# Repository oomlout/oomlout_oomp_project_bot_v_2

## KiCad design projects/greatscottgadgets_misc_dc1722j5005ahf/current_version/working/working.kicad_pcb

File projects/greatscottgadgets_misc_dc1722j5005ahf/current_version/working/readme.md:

# misc
 
## summary 
* id: greatscottgadgets_misc_dc1722j5005ahf
* user: greatscottgadgets
* name: misc
* board: dc1722j5005ahf
* repo: https://github.com/greatscottgadgets/misc
* src_file_repo_kicad_pcb: evaluation-boards/DC1722J5005AHF/DC1722J5005AHF.kicad_pcb
* src_file_repo_kicad_pcb_link: https://github.com/greatscottgadgets/misc/tree/master/evaluation-boards/DC1722J5005AHF/DC1722J5005AHF.kicad_pcb

* src_file_repo_sch: evaluation-boards/DC1722J5005AHF/DC1722J5005AHF.sch
* src_file_repo_sch_link: https://github.com/greatscottgadgets/misc/tree/master/evaluation-boards/DC1722J5005AHF/DC1722J5005AHF.sch
* full details link: https://github.com/oomlout/oomlout_oomp_project_bot_v_2/tree/main/projects/greatscottgadgets_misc_dc1722j5005ahf/current_version/working

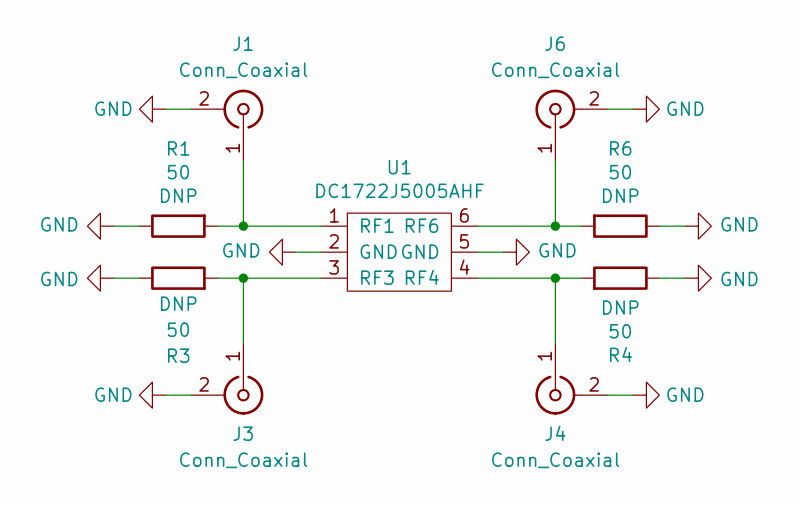
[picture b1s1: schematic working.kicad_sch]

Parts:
J1, J3, J4, J6: Conn_Coaxial; SMA-73251-2120
R1, R3, R4, R6: 50; R_0402_1005Metric
U1: DC1722J5005AHF; Anaren_0805_2012Metric-6

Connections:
GND: J1.2 (Ext), J3.2 (Ext), J4.2 (Ext), J6.2 (Ext), R1.1, R3.1, R4.1, R6.1, U1.2 (GND), U1.5 (GND)
unnamed: J1.1 (In), R1.2, U1.1 (RF1)
unnamed: J3.1 (In), R3.2, U1.3 (RF3)
unnamed: J4.1 (In), R4.2, U1.4 (RF4)
unnamed: J6.1 (In), R6.2, U1.6 (RF6)

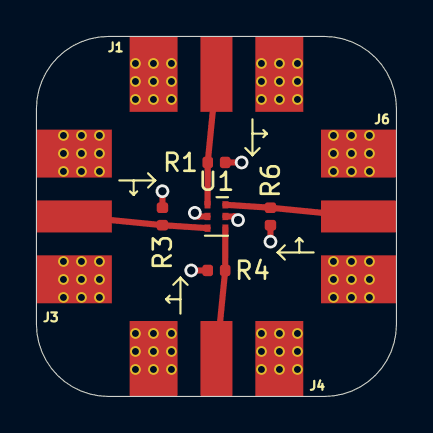
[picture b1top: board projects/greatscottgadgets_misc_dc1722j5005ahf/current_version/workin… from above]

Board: 4 copper layers, 20.0 x 20.0 mm, 9 parts (0 on the bottom side), 5 nets.

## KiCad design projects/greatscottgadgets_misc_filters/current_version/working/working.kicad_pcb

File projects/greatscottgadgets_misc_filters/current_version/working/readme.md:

# misc
 
## summary 
* id: greatscottgadgets_misc_filters
* user: greatscottgadgets
* name: misc
* board: filters
* repo: https://github.com/greatscottgadgets/misc
* src_file_repo_kicad_pcb: evaluation-boards/filters/filters.kicad_pcb
* src_file_repo_kicad_pcb_link: https://github.com/greatscottgadgets/misc/tree/master/evaluation-boards/filters/filters.kicad_pcb

* src_file_repo_sch: evaluation-boards/filters/filters.sch
* src_file_repo_sch_link: https://github.com/greatscottgadgets/misc/tree/master/evaluation-boards/filters/filters.sch
* full details link: https://github.com/oomlout/oomlout_oomp_project_bot_v_2/tree/main/projects/greatscottgadgets_misc_filters/current_version/working

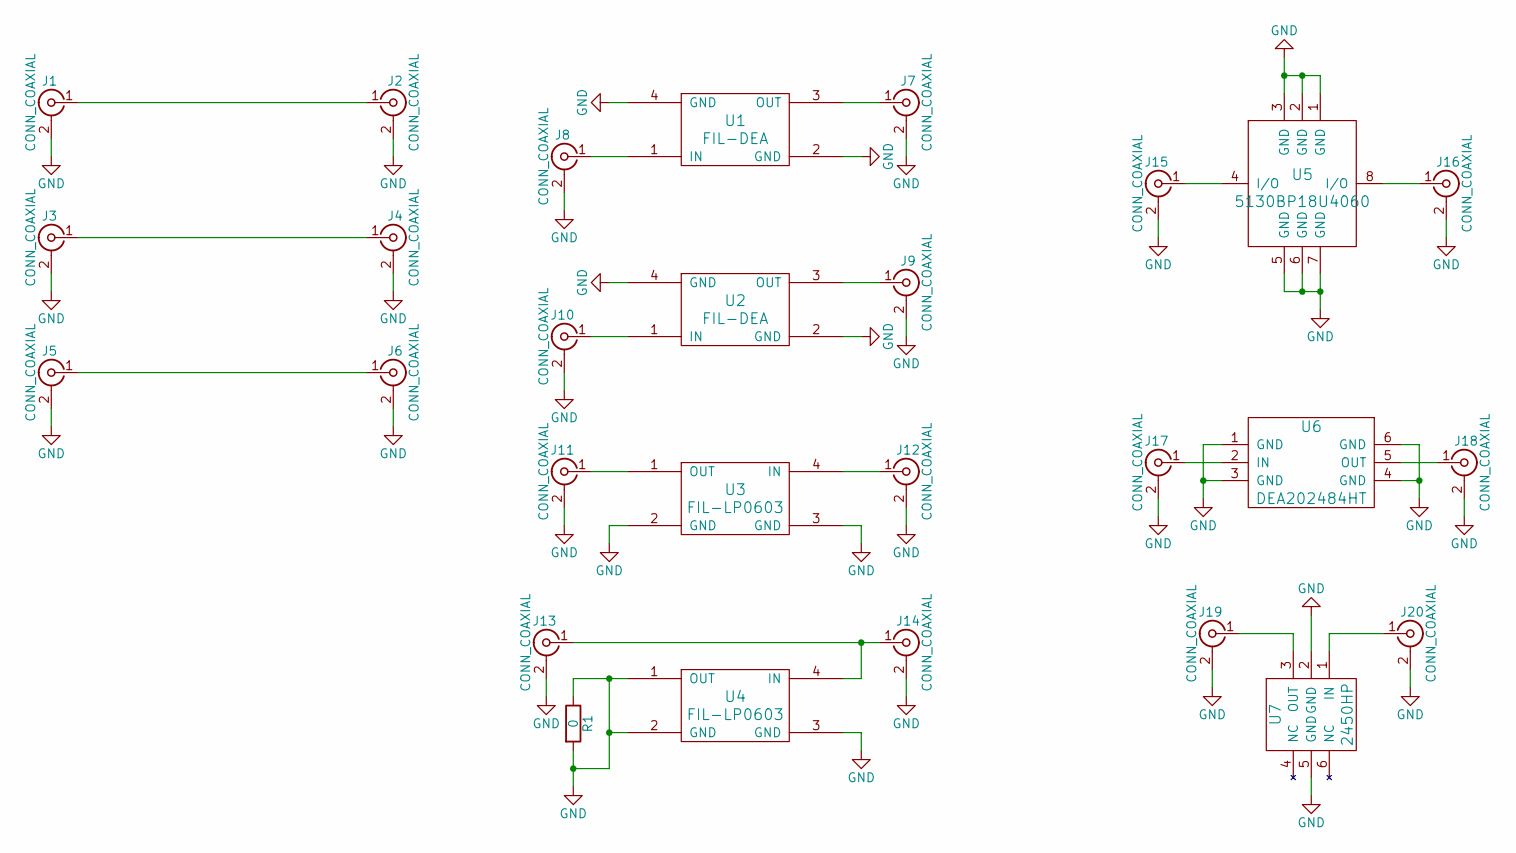
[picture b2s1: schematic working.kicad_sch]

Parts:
J1, J2, J3, J4, J5, J6, J7, J8, J9, J10, J11, J12, J13, J14, J15, J16, J17, J18, J19, J20: CONN_COAXIAL; SMA-EDGE
R1: 0; 0402
U1, U2: FIL-DEA; FIL-DEA-0603
U3, U4: FIL-LP0603; LP0603
U5: 5130BP18U4060
U6: DEA202484HT
U7: 2450HP; 2500BL14M100

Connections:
GND: J1.2 (Ext), J2.2 (Ext), J3.2 (Ext), J4.2 (Ext), J5.2 (Ext), J6.2 (Ext), J7.2 (Ext), J8.2 (Ext), J9.2 (Ext), J10.2 (Ext), J11.2 (Ext), J12.2 (Ext), J13.2 (Ext), J14.2 (Ext), J15.2 (Ext), J16.2 (Ext), J17.2 (Ext), J18.2 (Ext), J19.2 (Ext), J20.2 (Ext), R1.1, R1.2, U1.2 (GND), U1.4 (GND), U2.2 (GND), U2.4 (GND), U3.2 (GND), U3.3 (GND), U4.1 (OUT), U4.2 (GND), U4.3 (GND), U5.1 (GND), U5.2 (GND), U5.3 (GND), U5.5 (GND), U5.6 (GND), U5.7 (GND), U6.1 (GND), U6.3 (GND), U6.4 (GND), U6.6 (GND), U7.2 (GND), U7.5 (GND)
unnamed: J1.1 (In), J2.1 (In)
unnamed: J3.1 (In), J4.1 (In)
unnamed: J5.1 (In), J6.1 (In)
unnamed: J7.1 (In), U1.3 (OUT)
unnamed: J8.1 (In), U1.1 (IN)
unnamed: J9.1 (In), U2.3 (OUT)
unnamed: J10.1 (In), U2.1 (IN)
unnamed: J11.1 (In), U3.1 (OUT)
unnamed: J12.1 (In), U3.4 (IN)
unnamed: J13.1 (In), J14.1 (In), U4.4 (IN)
unnamed: J15.1 (In), U5.4 (I/O)
unnamed: J16.1 (In), U5.8 (I/O)
unnamed: J17.1 (In), U6.2 (IN)
unnamed: J18.1 (In), U6.5 (OUT)
unnamed: J19.1 (In), U7.3 (OUT)
unnamed: J20.1 (In), U7.1 (IN)

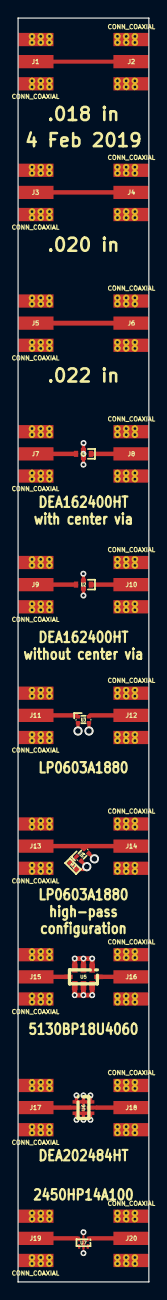
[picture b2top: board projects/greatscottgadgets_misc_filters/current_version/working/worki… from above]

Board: 4 copper layers, 15.0 x 145.0 mm, 28 parts (0 on the bottom side), 17 nets.

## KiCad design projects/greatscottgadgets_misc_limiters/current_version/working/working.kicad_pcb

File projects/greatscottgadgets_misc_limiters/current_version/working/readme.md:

# misc
 
## summary 
* id: greatscottgadgets_misc_limiters
* user: greatscottgadgets
* name: misc
* board: limiters
* repo: https://github.com/greatscottgadgets/misc
* src_file_repo_kicad_pcb: evaluation-boards/limiters/limiters.kicad_pcb
* src_file_repo_kicad_pcb_link: https://github.com/greatscottgadgets/misc/tree/master/evaluation-boards/limiters/limiters.kicad_pcb
* src_file_repo_kicad_sch: evaluation-boards/limiters/limiters.kicad_sch
* src_file_repo_kicad_sch_link: https://github.com/greatscottgadgets/misc/tree/master/evaluation-boards/limiters/limiters.kicad_sch

* src_file_repo_sch: evaluation-boards/limiters/limiters.sch
* src_file_repo_sch_link: https://github.com/greatscottgadgets/misc/tree/master/evaluation-boards/limiters/limiters.sch
* full details link: https://github.com/oomlout/oomlout_oomp_project_bot_v_2/tree/main/projects/greatscottgadgets_misc_limiters/current_version/working

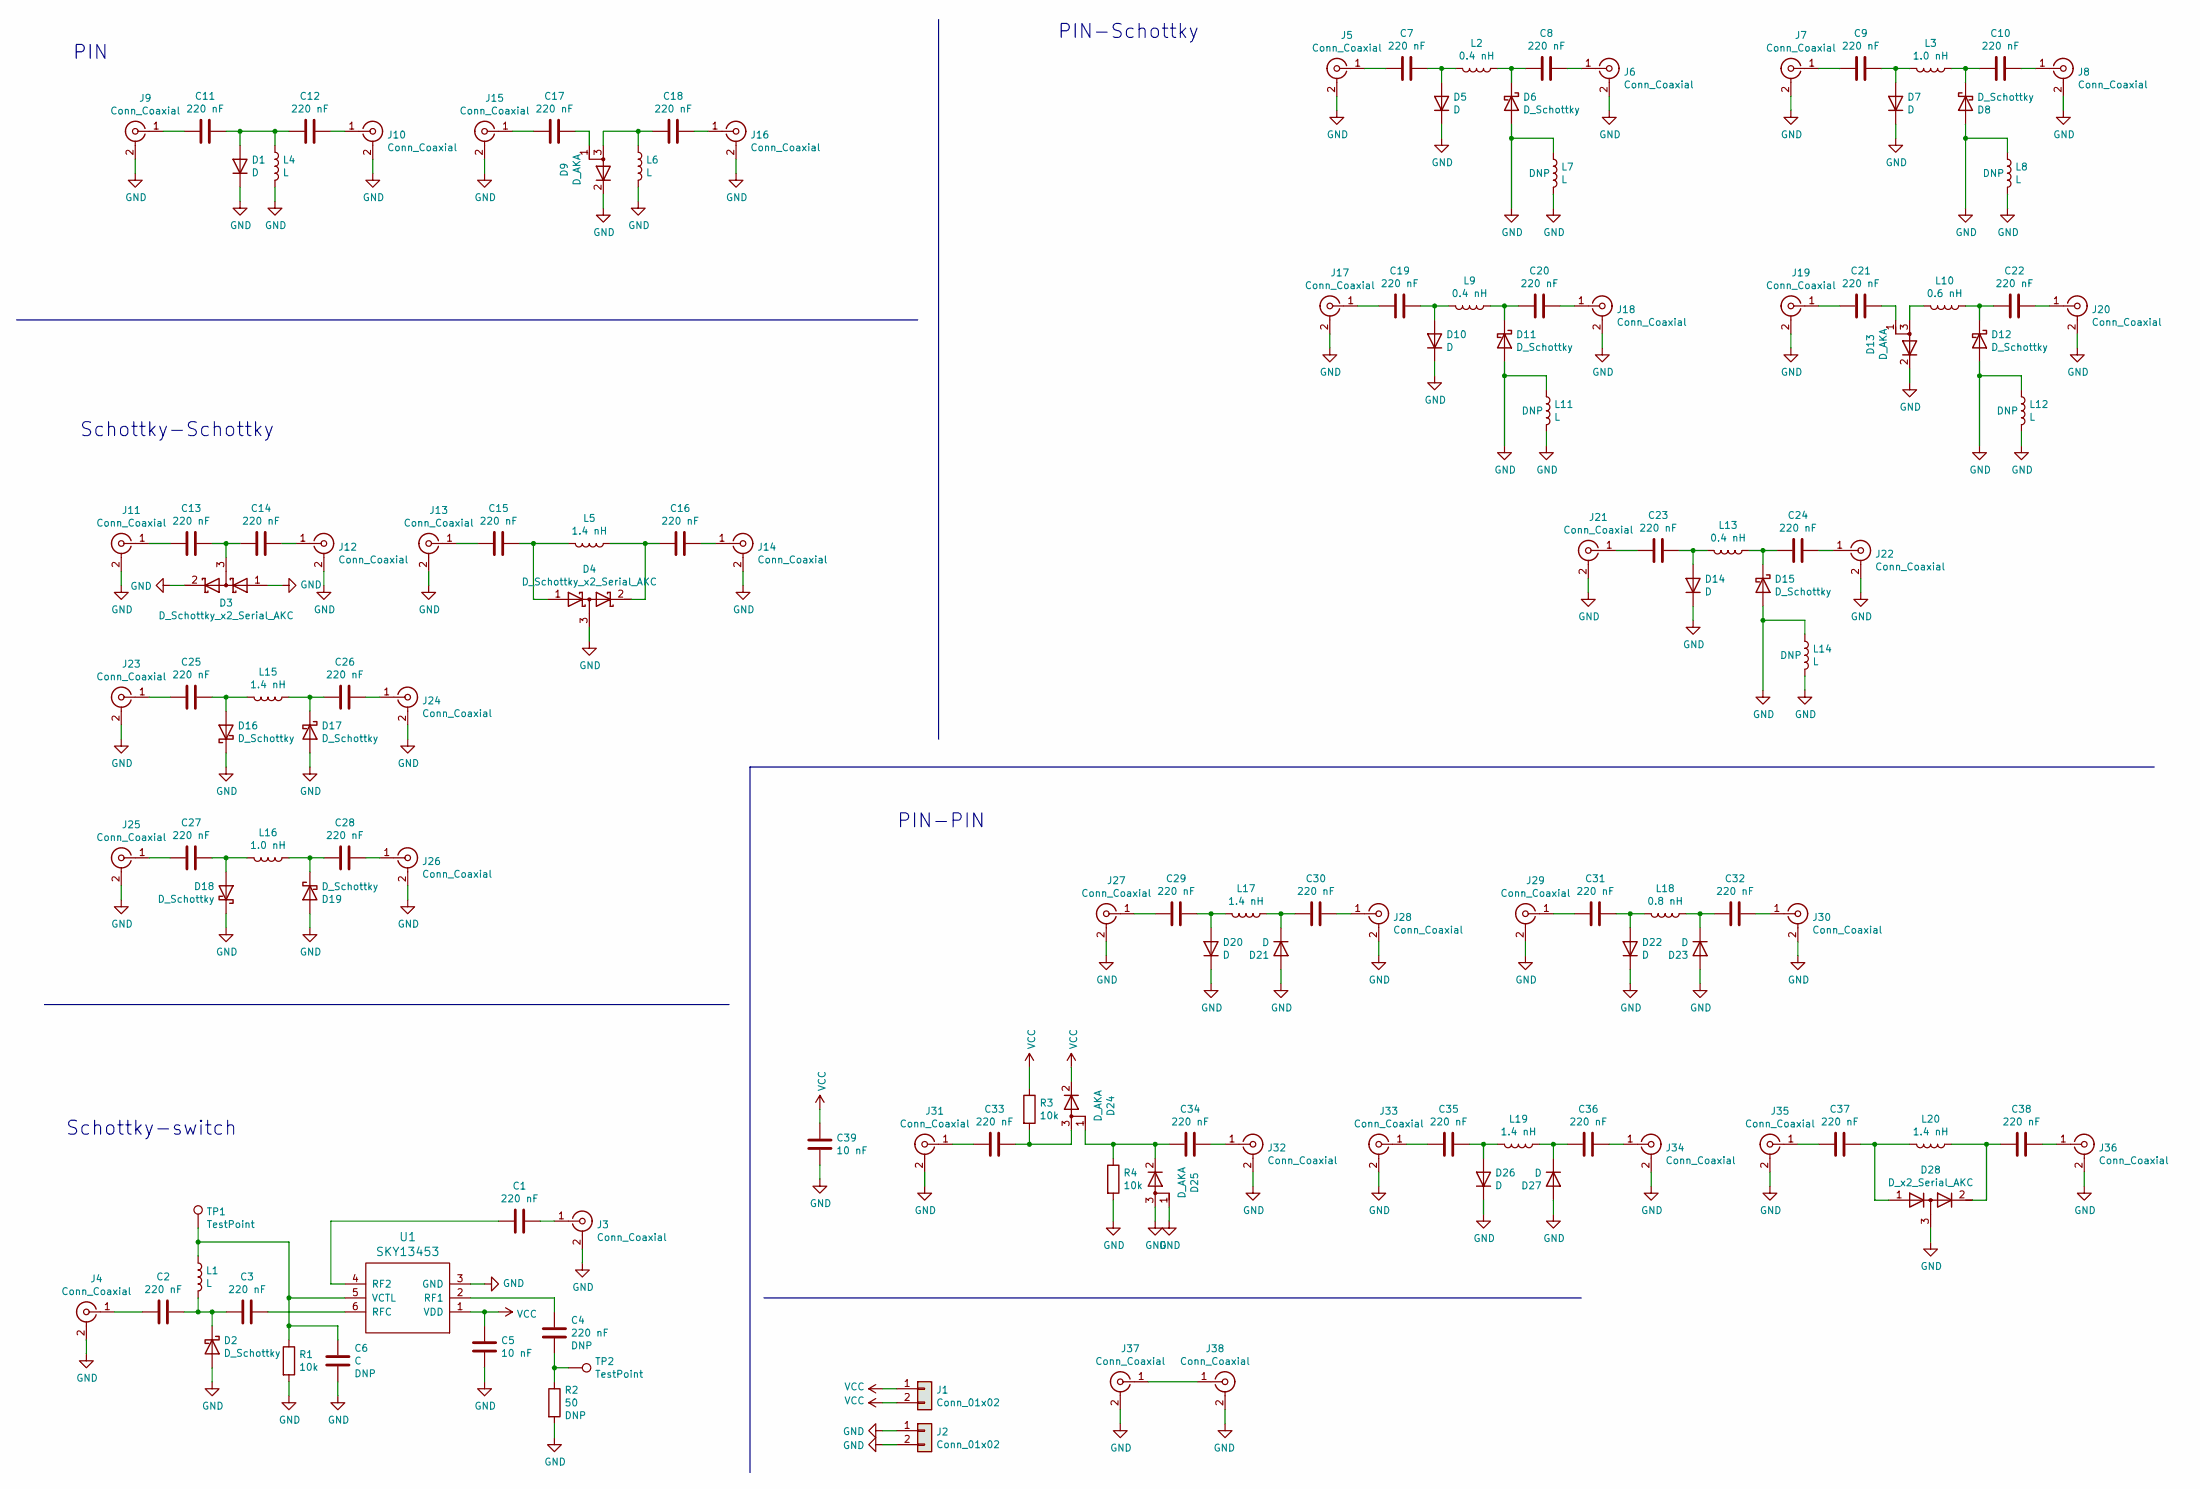
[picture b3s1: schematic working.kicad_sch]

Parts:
C1, C2, C3, C4, C7, C8, C9, C10, C11, C12, C13, C14, C15, C16, C17, C18, C19, C20, C21, C22, C23, C24, C25, C26, C27, C28, C29, C30, C31, C32, C33, C34, C35, C36, C37, C38: 220 nF; C_0201_0603Metric_Pad0.64x0.40mm_HandSolder; Part Number GRM033R61A224KE90D
C5, C39: 10 nF; C_0402_1005Metric_Pad0.74x0.62mm_HandSolder
C6: C; C_0402_1005Metric_Pad0.74x0.62mm_HandSolder
D1, D14, D22, D23: D; SMP1345-087LF; Part Number SMP1345-087LF
D2, D6, D11, D12, D15, D16, D17: D_Schottky; D_SOD-923; Part Number JDH2S02FSTPL3
D3, D4: D_Schottky_x2_Serial_AKC; SOT-23; Part Number BAT1504RE6152HTSA1
D5, D20, D21: D; D_0201_0603Metric_Pad0.64x0.40mm_HandSolder; Part Number NSDP301MX3T5G
D7: D; D_0201_0603Metric_Pad0.64x0.40mm_HandSolder; Part Number BAR9002ELSE6327XTSA1
D8, D18, D19: D_Schottky; D_0201_0603Metric_Pad0.64x0.40mm_HandSolder; Part Number BAT2402LSE6327XTSA1
D9, D13, D24, D25: D_AKA; SMP1304-085LF; Part Number SMP1304-085LF
D10, D26, D27: D; D_0402_1005Metric_Pad0.77x0.64mm_HandSolder; Part Number SMP1302-040LF
D28: D_x2_Serial_AKC; SOT-23; Part Number SMP1304-005LF
J1, J2: Conn_01x02; PinHeader_1x02_P2.54mm_Vertical
J3, J4, J5, J6, J7, J8, J9, J10, J11, J12, J13, J14, J15, J16, J17, J18, J19, J20, J21, J22, J23, J24, J25, J26, J27, J28, J29, J30, J31, J32, J33, J34, J35, J36, J37, J38: Conn_Coaxial; SMA-EDGE; Part Number CONSMA003.062
L1, L4, L6, L7, L8, L11, L12, L14: L; L_0603_1608Metric_Pad1.05x0.95mm_HandSolder; Part Number BRL1608T100M
L2, L9, L13: 0.4 nH; L_0201_0603Metric_Pad0.64x0.40mm_HandSolder; Part Number LQP03HQ0N4W02D
L3, L16: 1.0 nH; L_0201_0603Metric_Pad0.64x0.40mm_HandSolder; Part Number LQP03HQ1N0W02D
L5, L15, L17, L19, L20: 1.4 nH; L_0201_0603Metric_Pad0.64x0.40mm_HandSolder; Part Number LQP03HQ1N4W02D
L10: 0.6 nH; L_0201_0603Metric_Pad0.64x0.40mm_HandSolder; Part Number LQP03HQ0N6W02D
L18: 0.8 nH; L_0201_0603Metric_Pad0.64x0.40mm_HandSolder; Part Number LQP03HQ0N8W02D
R1, R3, R4: 10k; R_0402_1005Metric_Pad0.72x0.64mm_HandSolder
R2: 50; R_0402_1005Metric_Pad0.72x0.64mm_HandSolder
TP1, TP2: TestPoint; TESTPOINT-50MIL
U1: SKY13453; SKY13350-385LF; Part Number SKY13453-385LF

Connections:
GND: C5.1, C6.2, C39.1, D1.1 (K), D2.2 (A), D3.1 (A), D3.2 (K), D4.3 (common), D5.1 (K), D6.2 (A), D7.1 (K), D8.2 (A), D9.2 (K), D10.1 (K), D11.2 (A), D12.2 (A), D13.2 (K), D14.1 (K), D15.2 (A), D16.1 (K), D17.2 (A), D18.1 (K), D19.2 (A), D20.1 (K), D21.2 (A), D22.1 (K), D23.2 (A), D25.1 (A), D25.3 (A), D26.1 (K), D27.2 (A), D28.3 (common), J2.1, J2.2, J3.2 (Ext), J4.2 (Ext), J5.2 (Ext), J6.2 (Ext), J7.2 (Ext), J8.2 (Ext), J9.2 (Ext), J10.2 (Ext), J11.2 (Ext), J12.2 (Ext), J13.2 (Ext), J14.2 (Ext), J15.2 (Ext), J16.2 (Ext), J17.2 (Ext), J18.2 (Ext), J19.2 (Ext), J20.2 (Ext), J21.2 (Ext), J22.2 (Ext), J23.2 (Ext), J24.2 (Ext), J25.2 (Ext), J26.2 (Ext), J27.2 (Ext), J28.2 (Ext), J29.2 (Ext), J30.2 (Ext), J31.2 (Ext), J32.2 (Ext), J33.2 (Ext), J34.2 (Ext), J35.2 (Ext), J36.2 (Ext), J37.2 (Ext), J38.2 (Ext), L4.2, L6.2, L7.1, L7.2, L8.1, L8.2, L11.1, L11.2, L12.1, L12.2, L14.1, L14.2, R1.2, R2.2, R4.2, U1.3 (GND)
unnamed: C1.1, J3.1 (In)
unnamed: C1.2, U1.4 (RF2)
unnamed: C2.1, C3.2, D2.1 (K), L1.2
unnamed: C2.2, J4.1 (In)
unnamed: C3.1, U1.6 (RFC)
unnamed: C4.1, R2.1, TP2.1
unnamed: C4.2, U1.2 (RF1)
unnamed: C6.1, L1.1, R1.1, TP1.1, U1.5 (VCTL)
unnamed: C7.1, D5.2 (A), L2.2
unnamed: C7.2, J5.1 (In)
unnamed: C8.1, J6.1 (In)
unnamed: C8.2, D6.1 (K), L2.1
unnamed: C9.1, D7.2 (A), L3.2
unnamed: C9.2, J7.1 (In)
unnamed: C10.1, J8.1 (In)
unnamed: C10.2, D8.1 (K), L3.1
unnamed: C11.1, C12.2, D1.2 (A), L4.1
unnamed: C11.2, J9.1 (In)
unnamed: C12.1, J10.1 (In)
unnamed: C13.1, C14.2, D3.3 (common)
unnamed: C13.2, J11.1 (In)
unnamed: C14.1, J12.1 (In)
unnamed: C15.1, D4.1 (A), L5.2
unnamed: C15.2, J13.1 (In)
unnamed: C16.1, J14.1 (In)
unnamed: C16.2, D4.2 (K), L5.1
unnamed: C17.1, D9.1 (A)
unnamed: C17.2, J15.1 (In)
unnamed: C18.1, J16.1 (In)
unnamed: C18.2, D9.3 (A), L6.1
unnamed: C19.1, D10.2 (A), L9.2
unnamed: C19.2, J17.1 (In)
unnamed: C20.1, J18.1 (In)
unnamed: C20.2, D11.1 (K), L9.1
unnamed: C21.1, D13.1 (A)
unnamed: C21.2, J19.1 (In)
unnamed: C22.1, J20.1 (In)
unnamed: C22.2, D12.1 (K), L10.1
unnamed: C23.1, D14.2 (A), L13.2
unnamed: C23.2, J21.1 (In)
unnamed: C24.1, J22.1 (In)
unnamed: C24.2, D15.1 (K), L13.1
unnamed: C25.1, D16.2 (A), L15.2
unnamed: C25.2, J23.1 (In)
unnamed: C26.1, J24.1 (In)
unnamed: C26.2, D17.1 (K), L15.1
unnamed: C27.1, D18.2 (A), L16.2
unnamed: C27.2, J25.1 (In)
unnamed: C28.1, J26.1 (In)
unnamed: C28.2, D19.1 (K), L16.1
unnamed: C29.1, D20.2 (A), L17.2
unnamed: C29.2, J27.1 (In)
unnamed: C30.1, J28.1 (In)
unnamed: C30.2, D21.1 (K), L17.1
unnamed: C31.1, D22.2 (A), L18.2
unnamed: C31.2, J29.1 (In)
unnamed: C32.1, J30.1 (In)
unnamed: C32.2, D23.1 (K), L18.1
unnamed: C33.1, D24.3 (A), R3.2
unnamed: C33.2, J31.1 (In)
unnamed: C34.1, J32.1 (In)
unnamed: C34.2, D24.1 (A), D25.2 (K), R4.1
unnamed: C35.1, D26.2 (A), L19.2
unnamed: C35.2, J33.1 (In)
unnamed: C36.1, J34.1 (In)
unnamed: C36.2, D27.1 (K), L19.1
unnamed: C37.1, D28.1 (A), L20.2
unnamed: C37.2, J35.1 (In)
unnamed: C38.1, J36.1 (In)
unnamed: C38.2, D28.2 (K), L20.1
unnamed: D13.3 (A), L10.2
unnamed: J37.1 (In), J38.1 (In)
VCC: C5.2, C39.2, D24.2 (K), J1.1, J1.2, R3.1, U1.1 (VDD)

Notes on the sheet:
Schottky-switch
PIN-Schottky
PIN-PIN
PIN
Schottky-Schottky

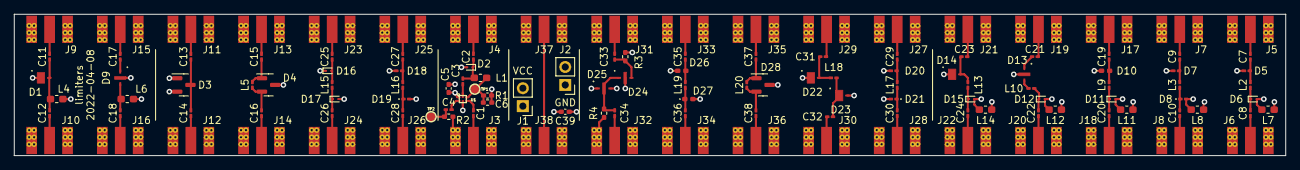
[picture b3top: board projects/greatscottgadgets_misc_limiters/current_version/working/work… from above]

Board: 4 copper layers, 180.0 x 20.0 mm, 132 parts (0 on the bottom side), 74 nets.

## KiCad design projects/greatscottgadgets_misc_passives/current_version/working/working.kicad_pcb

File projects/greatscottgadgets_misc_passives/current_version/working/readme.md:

# misc
 
## summary 
* id: greatscottgadgets_misc_passives
* user: greatscottgadgets
* name: misc
* board: passives
* repo: https://github.com/greatscottgadgets/misc
* src_file_repo_kicad_pcb: evaluation-boards/passives/passives.kicad_pcb
* src_file_repo_kicad_pcb_link: https://github.com/greatscottgadgets/misc/tree/master/evaluation-boards/passives/passives.kicad_pcb
* src_file_repo_kicad_sch: evaluation-boards/passives/passives.kicad_sch
* src_file_repo_kicad_sch_link: https://github.com/greatscottgadgets/misc/tree/master/evaluation-boards/passives/passives.kicad_sch

* src_file_repo_sch: evaluation-boards/passives/passives.sch
* src_file_repo_sch_link: https://github.com/greatscottgadgets/misc/tree/master/evaluation-boards/passives/passives.sch
* full details link: https://github.com/oomlout/oomlout_oomp_project_bot_v_2/tree/main/projects/greatscottgadgets_misc_passives/current_version/working

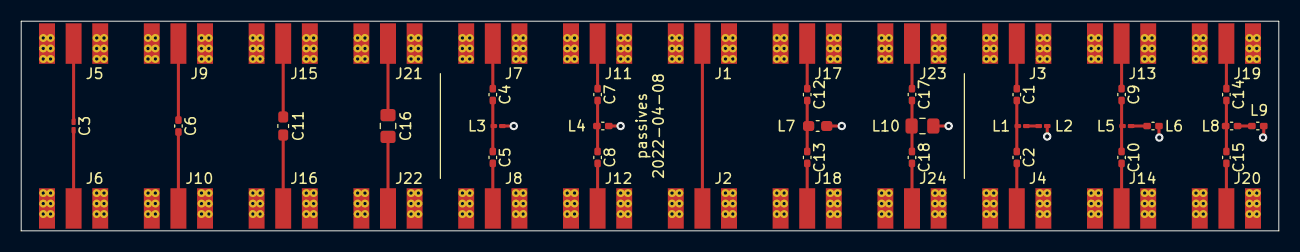
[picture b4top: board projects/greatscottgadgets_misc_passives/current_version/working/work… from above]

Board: 4 copper layers, 120.0 x 20.0 mm, 52 parts (0 on the bottom side), 34 nets.

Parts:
C1, C2, C4, C5, C6, C7, C8, C9, C10, C12, C13, C14, C15, C17, C18: C; C_0402_1005Metric_Pad0.74x0.62mm_HandSolder
C3: C; C_0201_0603Metric_Pad0.64x0.40mm_HandSolder
C11: C; C_0603_1608Metric_Pad1.08x0.95mm_HandSolder
C16: C; C_0805_2012Metric_Pad1.18x1.45mm_HandSolder
J1, J2, J3, J4, J5, J6, J7, J8, J9, J10, J11, J12, J13, J14, J15, J16, J17, J18, J19, J20, J21, J22, J23, J24: Conn_Coaxial; SMA-EDGE
L1, L2, L3, L5: L; C_0201_0603Metric_Pad0.64x0.40mm_HandSolder
L4, L6, L8, L9: L; C_0402_1005Metric_Pad0.74x0.62mm_HandSolder
L7: L; C_0603_1608Metric_Pad1.08x0.95mm_HandSolder
L10: L; C_0805_2012Metric_Pad1.18x1.45mm_HandSolder

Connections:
GND: J1.2 (Ext), J2.2 (Ext), J3.2 (Ext), J4.2 (Ext), J5.2 (Ext), J6.2 (Ext), J7.2 (Ext), J8.2 (Ext), J9.2 (Ext), J10.2 (Ext), J11.2 (Ext), J12.2 (Ext), J13.2 (Ext), J14.2 (Ext), J15.2 (Ext), J16.2 (Ext), J17.2 (Ext), J18.2 (Ext), J19.2 (Ext), J20.2 (Ext), J21.2 (Ext), J22.2 (Ext), J23.2 (Ext), J24.2 (Ext), L2.2, L3.2, L4.2, L6.2, L7.2, L9.2, L10.2
unnamed: C1.1, J3.1 (In)
unnamed: C1.2, C2.1, L1.1
unnamed: C2.2, J4.1 (In)
unnamed: C3.1, J5.1 (In)
unnamed: C3.2, J6.1 (In)
unnamed: C4.1, J7.1 (In)
unnamed: C4.2, C5.1, L3.1
unnamed: C5.2, J8.1 (In)
unnamed: C6.1, J9.1 (In)
unnamed: C6.2, J10.1 (In)
unnamed: C7.1, J11.1 (In)
unnamed: C7.2, C8.1, L4.1
unnamed: C8.2, J12.1 (In)
unnamed: C9.1, J13.1 (In)
unnamed: C9.2, C10.1, L5.1
unnamed: C10.2, J14.1 (In)
unnamed: C11.1, J15.1 (In)
unnamed: C11.2, J16.1 (In)
unnamed: C12.1, J17.1 (In)
unnamed: C12.2, C13.1, L7.1
unnamed: C13.2, J18.1 (In)
unnamed: C14.1, J19.1 (In)
unnamed: C14.2, C15.1, L8.1
unnamed: C15.2, J20.1 (In)
unnamed: C16.1, J21.1 (In)
unnamed: C16.2, J22.1 (In)
unnamed: C17.1, J23.1 (In)
unnamed: C17.2, C18.1, L10.1
unnamed: C18.2, J24.1 (In)
unnamed: J1.1 (In), J2.1 (In)
unnamed: L1.2, L2.1
unnamed: L5.2, L6.1
unnamed: L8.2, L9.1

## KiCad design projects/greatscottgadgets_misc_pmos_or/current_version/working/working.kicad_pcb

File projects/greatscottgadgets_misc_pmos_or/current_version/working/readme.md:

# misc
 
## summary 
* id: greatscottgadgets_misc_pmos_or
* user: greatscottgadgets
* name: misc
* board: pmos_or
* repo: https://github.com/greatscottgadgets/misc
* src_file_repo_kicad_pcb: evaluation-boards/pmos-or/pmos-or.kicad_pcb
* src_file_repo_kicad_pcb_link: https://github.com/greatscottgadgets/misc/tree/master/evaluation-boards/pmos-or/pmos-or.kicad_pcb
* src_file_repo_kicad_sch: evaluation-boards/pmos-or/pmos-or.kicad_sch
* src_file_repo_kicad_sch_link: https://github.com/greatscottgadgets/misc/tree/master/evaluation-boards/pmos-or/pmos-or.kicad_sch

* src_file_repo_sch: evaluation-boards/passives/passives.sch
* src_file_repo_sch_link: https://github.com/greatscottgadgets/misc/tree/master/evaluation-boards/passives/passives.sch
* full details link: https://github.com/oomlout/oomlout_oomp_project_bot_v_2/tree/main/projects/greatscottgadgets_misc_pmos_or/current_version/working

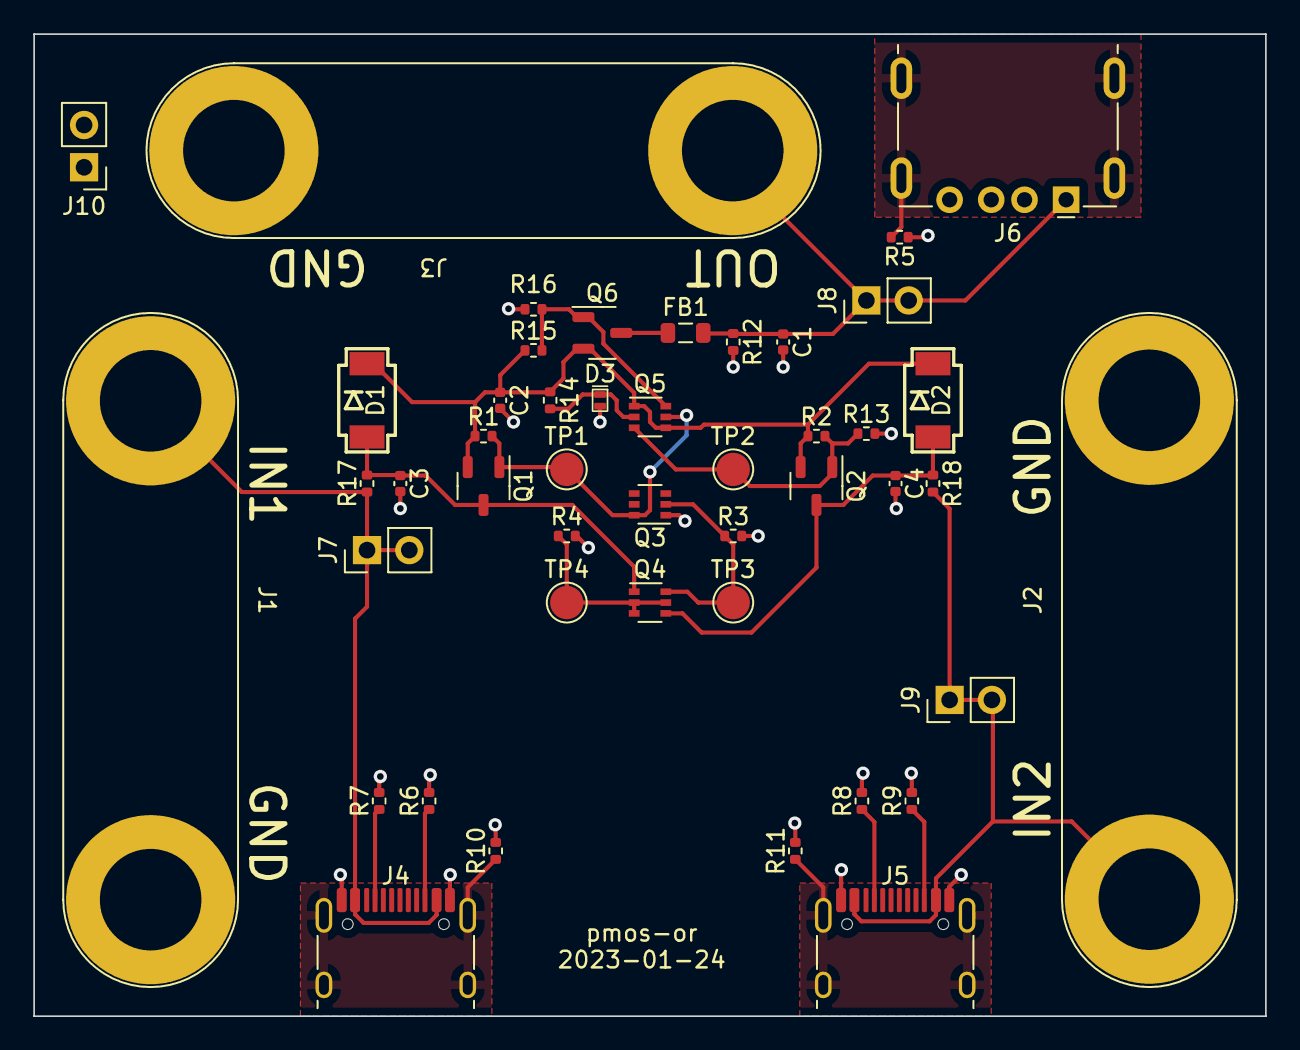
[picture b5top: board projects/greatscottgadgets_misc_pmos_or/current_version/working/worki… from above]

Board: 2 copper layers, 74.0 x 59.0 mm, 46 parts (0 on the bottom side), 21 nets.

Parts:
C1, C2, C3, C4: 100nF; C_0402_1005Metric
D1, D2: D; SOD128
D3: 4.7±2%; DFN1006-2
FB1: FerriteBead; L_0805_2012Metric
J1: IN1; Banana_Jack_2Pin
J2: IN2; Banana_Jack_2Pin
J3: OUT; Banana_Jack_2Pin
J4, J5: USB_C_Receptacle_USB2.0; USB_C_Receptacle_HRO_TYPE-C-31-M-12
J6: USB_A; USB_A_Kycon_KUSBXHT-SB-AS1N-B30-NF_Horizontal
J7: IN1; PinHeader_1x02_P2.54mm_Vertical
J8: OUT; PinHeader_1x02_P2.54mm_Vertical
J9: IN2; PinHeader_1x02_P2.54mm_Vertical
J10: GND; PinHeader_1x02_P2.54mm_Vertical
Q1, Q2, Q6: PMOS; SOT-23-3
Q3: 2NMOS; SOT-363_SC-70-6
Q4: 2PNP; SOT-363_SC-70-6
Q5: 2PMOS; SOT-363_SC-70-6
R1, R3, R4, R13, R16: 10k; R_0402_1005Metric
R2, R15: 20k; R_0402_1005Metric
R5, R10, R11, R17, R18: 0; R_0402_1005Metric
R6, R7, R8, R9: 5.1k; R_0402_1005Metric
R12: R; R_0402_1005Metric
R14: 1k; R_0402_1005Metric
TP1, TP2, TP3, TP4: TestPoint; TestPoint_Pad_D2.0mm

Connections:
/BASE: Q4.2 (B1), Q4.3 (C2), Q4.5 (B2), R4.1, TP4.1
/CTRL: Q3.2 (G), Q4.6 (C1), R3.1, TP3.1
/G1: Q1.1 (G), Q3.6 (D), Q5.5 (G), R1.2, TP1.1
/G2: Q2.1 (G), Q5.3 (D), R2.2, R13.1, TP2.1
/IN1: J1.2, J4.A4 (VBUS), J4.A9 (VBUS), J4.B4 (VBUS), J4.B9 (VBUS), J7.1, J7.2, R17.1
/IN2: J2.2, J5.A4 (VBUS), J5.A9 (VBUS), J5.B4 (VBUS), J5.B9 (VBUS), J9.1, J9.2, R18.2
/OUT: C1.1, FB1.2, J3.2, J6.1 (VBUS), J8.1, J8.2, R12.1
/VBUS: C2.1, D1.1 (K), D2.1 (K), Q1.2 (S), Q2.2 (S), Q5.1 (S), Q5.4 (S), Q6.2 (S), R1.1, R2.1, R14.1, R15.1
GND: C1.2, C2.2, C3.2, C4.2, D3.2 (A), J1.1, J2.1, J3.1, J4.A1 (GND), J4.A12 (GND), J4.B1 (GND), J4.B12 (GND), J5.A1 (GND), J5.A12 (GND), J5.B1 (GND), J5.B12 (GND), J6.4 (GND), J10.1, J10.2, Q3.1 (S), R3.2, R4.2, R5.1, R6.2, R7.2, R8.2, R9.2, R10.2, R11.2, R12.2, R13.2, R16.2
unnamed: C3.1, D1.2 (A), Q1.3 (D), Q4.1 (E1), R17.2
unnamed: C4.1, D2.2 (A), Q2.3 (D), Q4.4 (E2), R18.1
unnamed: D3.1 (K), Q5.2 (G), R14.2
unnamed: FB1.1, Q6.3 (D)
unnamed: J4.A5 (CC1), R7.1
unnamed: J4.B5 (CC2), R6.1
unnamed: J4.S1 (SHIELD), R10.1
unnamed: J5.A5 (CC1), R8.1
unnamed: J5.B5 (CC2), R9.1
unnamed: J5.S1 (SHIELD), R11.1
unnamed: J6.5 (Shield), R5.2
unnamed: Q5.6 (D), Q6.1 (G), R15.2, R16.1

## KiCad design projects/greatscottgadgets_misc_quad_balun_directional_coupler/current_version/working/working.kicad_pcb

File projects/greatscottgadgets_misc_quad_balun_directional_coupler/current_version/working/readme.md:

# misc
 
## summary 
* id: greatscottgadgets_misc_quad_balun_directional_coupler
* user: greatscottgadgets
* name: misc
* board: quad_balun_directional_coupler
* repo: https://github.com/greatscottgadgets/misc
* src_file_repo_kicad_pcb: evaluation-boards/quad-balun-directional-coupler/quad-balun-directional-coupler.kicad_pcb
* src_file_repo_kicad_pcb_link: https://github.com/greatscottgadgets/misc/tree/master/evaluation-boards/quad-balun-directional-coupler/quad-balun-directional-coupler.kicad_pcb
* src_file_repo_kicad_sch: evaluation-boards/pmos-or/pmos-or.kicad_sch
* src_file_repo_kicad_sch_link: https://github.com/greatscottgadgets/misc/tree/master/evaluation-boards/pmos-or/pmos-or.kicad_sch

* src_file_repo_sch: evaluation-boards/quad-balun-directional-coupler/quad-balun-directional-coupler.sch
* src_file_repo_sch_link: https://github.com/greatscottgadgets/misc/tree/master/evaluation-boards/quad-balun-directional-coupler/quad-balun-directional-coupler.sch
* full details link: https://github.com/oomlout/oomlout_oomp_project_bot_v_2/tree/main/projects/greatscottgadgets_misc_quad_balun_directional_coupler/current_version/working

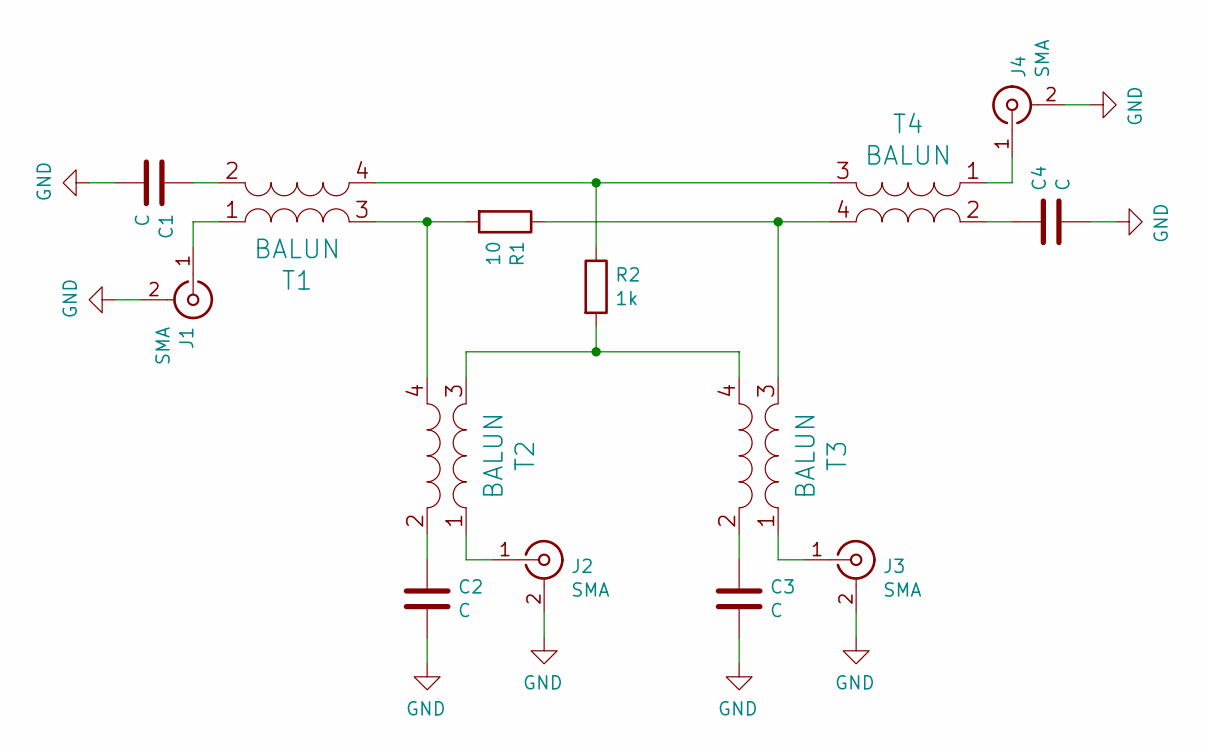
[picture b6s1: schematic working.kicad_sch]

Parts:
C1, C2, C3, C4: C; 0402
J1, J2, J3, J4: SMA; SMA-73251-2120
R1: 10; 0402
R2: 1k; 0402
T1, T2, T3, T4: BALUN; Anaren_0805_2012Metric-6; Part Number B0322J5050AHF

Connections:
GND: C1.2, C2.2, C3.2, C4.2, J1.2 (Ext), J2.2 (Ext), J3.2 (Ext), J4.2 (Ext)
unnamed: C1.1, T1.2 (S2)
unnamed: C2.1, T2.2 (S2)
unnamed: C3.1, T3.2 (S2)
unnamed: C4.1, T4.2 (S2)
unnamed: J1.1 (In), T1.1 (S1)
unnamed: J2.1 (In), T2.1 (S1)
unnamed: J3.1 (In), T3.1 (S1)
unnamed: J4.1 (In), T4.1 (S1)
unnamed: R1.1, T3.3 (PR1), T4.4 (PR2)
unnamed: R1.2, T1.3 (PR1), T2.4 (PR2)
unnamed: R2.1, T1.4 (PR2), T4.3 (PR1)
unnamed: R2.2, T2.3 (PR1), T3.4 (PR2)

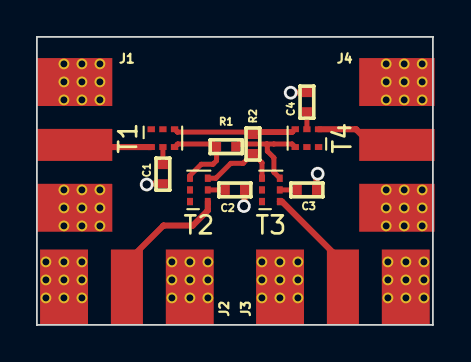
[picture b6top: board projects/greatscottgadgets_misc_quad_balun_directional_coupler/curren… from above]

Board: 4 copper layers, 22.0 x 16.0 mm, 14 parts (0 on the bottom side), 13 nets.
